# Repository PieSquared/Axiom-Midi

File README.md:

# Axiom-Midi
a Professional customizable MIDI Keyboard made by PieSquared. Has 1 octave worth of touch buttons (12 Key), 12 LEDs below them, 2 Push button rotary encoders, 6 Buttons, and a 0.96in LCD. Requires software to run and customize

## Why did I make this project

I mainly wanted to challenge myself and see what I could do without using a devkit, and what better way to do this by making something about what I love, Music!

Onshape Document: https://cad.onshape.com/documents/4fcb2e2092c7b8f6c2e7c126/w/a1f5aab5071a20b775f20b63/e/1a1cbc1f4bd564a001b92cae

## Features
- Customizable keys (Mainly used for soundboard)
- 12 touch keys
- 2 Pushbutton Rotary Encoders (Can be used for Octave changes, ect.)
- LCD
- Customizable LEDs
- Custom firmware
- Small formfactor

## Pictures

## BOM

| Part | Quantity |
|---|---:|
| 0.96 inch OLED IIC white 128x64 | 1 |
| EC11 rotary encoder right-angle with switch | 2 |
| Kailh Low Profile Choc switch 1350 clicky tactile | 6 |
| EC11 knob (half handle black) | 2 |
| CFX Low Profile Choc PBT keycaps | 6 |
|Case| 1 |
|PCB| 1 |

For purchase cost and purchase links refer to BOM.csv

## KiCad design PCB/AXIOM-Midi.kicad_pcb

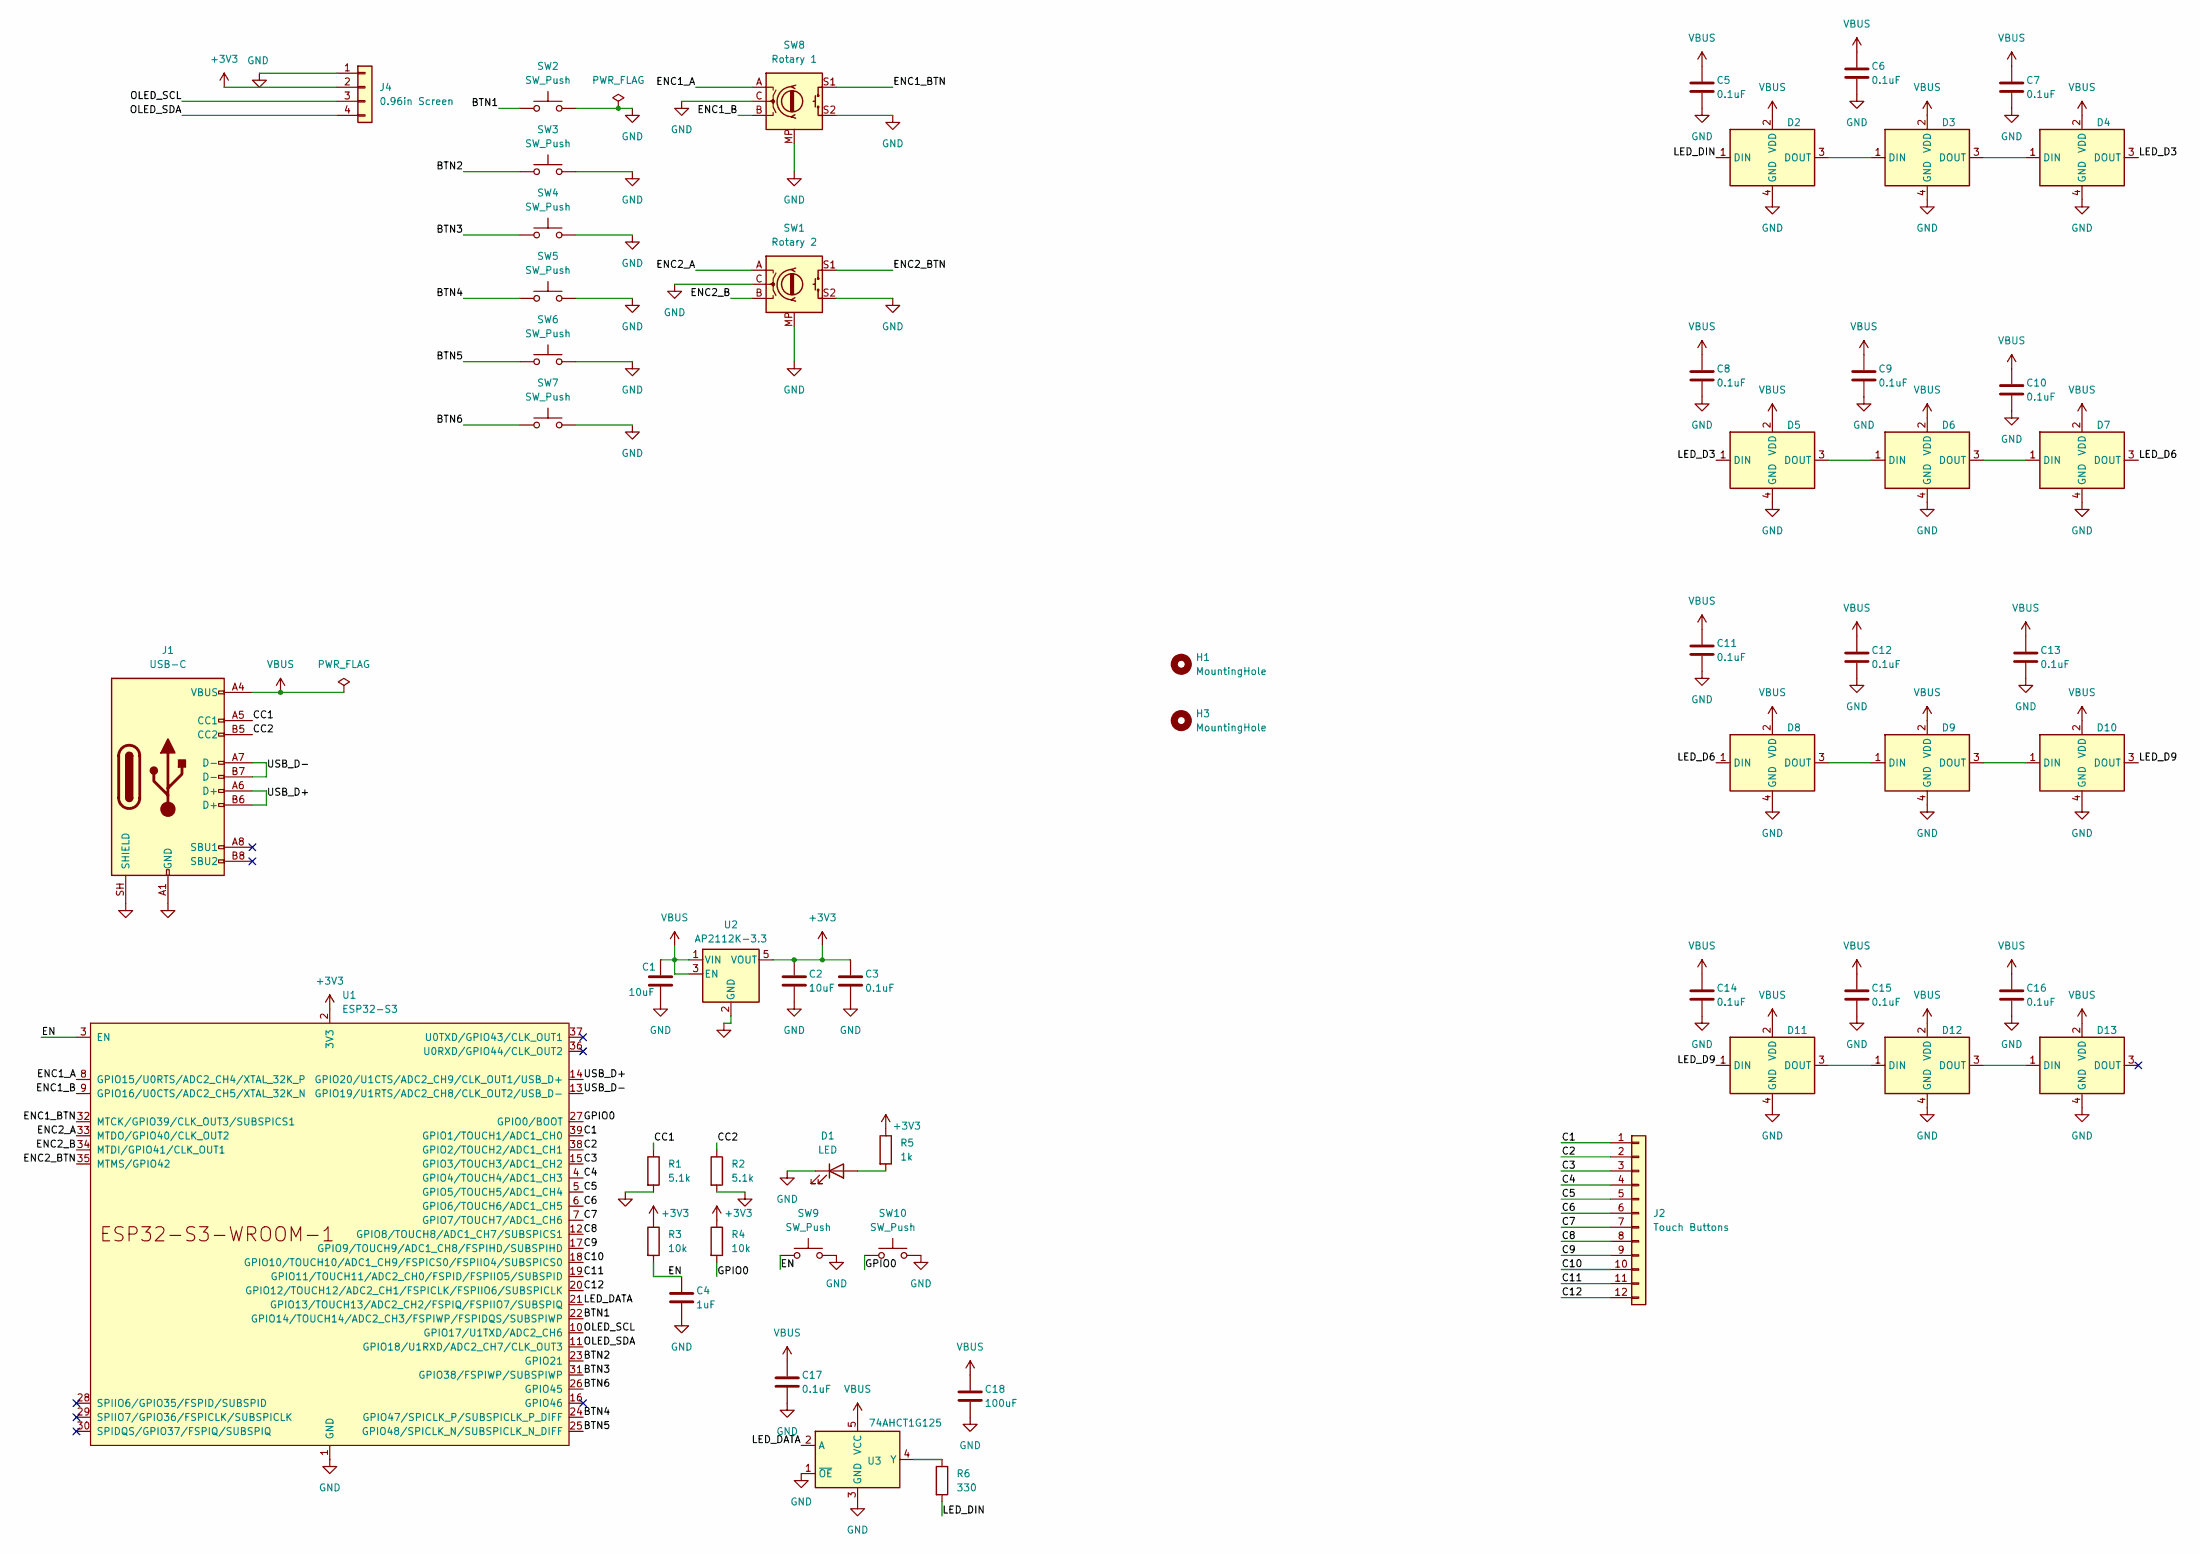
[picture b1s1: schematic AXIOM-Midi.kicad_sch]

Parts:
C1, C2: 10uF; C_0805_2012Metric
C3, C5, C6, C7, C8, C9, C10, C11, C12, C13, C14, C15, C16, C17: 0.1uF; C_0603_1608Metric
C4: 1uF; C_0603_1608Metric
C18: 100uF; CP_Elec_6.3x5.4
D1: LED; LED_0603_1608Metric
D2, D3, D4, D5, D6, D7, D8, D9, D10, D11, D12, D13: SK6812SIDE-A; LED-SMD_4P-L4.0-W1.6-L
H1, H3: MountingHole; MountingHole_3mm
J1: USB-C; USB_C_Receptacle_HRO_TYPE-C-31-M-12
J2: Touch Buttons; Piano_12Key
J4: 0.96in Screen; PinSocket_1x04_P2.54mm_Vertical
R1, R2: 5.1k; R_0603_1608Metric
R3, R4: 10k; R_0603_1608Metric
R5: 1k; R_0603_1608Metric
R6: 330; R_0603_1608Metric
SW1: Rotary 2; RotaryEncoder_Alps_EC11E-Switch_Vertical_H20mm
SW2, SW3, SW4, SW5, SW6, SW7: SW_Push; Kailh Choc Low-Profile Switches
SW8: Rotary 1; RotaryEncoder_Alps_EC11E-Switch_Vertical_H20mm
SW9, SW10: SW_Push; SW_SPST_TL3342
U1: ESP32-S3; ESP32-S3-WROOM-1
U2: AP2112K-3.3; SOT-23-5
U3: 74AHCT1G125; SOT-23-5

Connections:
+3V3: C2.1, C3.1, J4.2, R3.1, R4.1, R5.1, U1.2 (3V3), U2.5 (VOUT)
/BTN1: SW2.1, U1.22 (GPIO14/TOUCH14/ADC2_CH3/FSPIWP/FSPIDQS/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)
/BTN2: SW3.1, U1.23 (GPIO21)
/BTN3: SW4.1, U1.31 (GPIO38/FSPIWP/SUBSPIWP)
/BTN4: SW5.1, U1.24 (GPIO47/SPICLK_P/SUBSPICLK_P_DIFF)
/BTN5: SW6.1, U1.25 (GPIO48/SPICLK_N/SUBSPICLK_N_DIFF)
/BTN6: SW7.1, U1.26 (GPIO45)
/C1: J2.1, U1.39 (GPIO1/TOUCH1/ADC1_CH0)
/C2: J2.2, U1.38 (GPIO2/TOUCH2/ADC1_CH1)
/C3: J2.3, U1.15 (GPIO3/TOUCH3/ADC1_CH2)
/C4: J2.4, U1.4 (GPIO4/TOUCH4/ADC1_CH3)
/C5: J2.5, U1.5 (GPIO5/TOUCH5/ADC1_CH4)
/C6: J2.6, U1.6 (GPIO6/TOUCH6/ADC1_CH5)
/C7: J2.7, U1.7 (GPIO7/TOUCH7/ADC1_CH6)
/C8: J2.8, U1.12 (GPIO8/TOUCH8/ADC1_CH7/SUBSPICS1)
/C9: J2.9, U1.17 (GPIO9/TOUCH9/ADC1_CH8/FSPIHD/SUBSPIHD)
/C10: J2.10, U1.18 (GPIO10/TOUCH10/ADC1_CH9/FSPICS0/FSPIIO4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)
/C11: J2.11, U1.19 (GPIO11/TOUCH11/ADC2_CH0/FSPID/FSPIIO5/S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)
/C12: J2.12, U1.20 (GPIO12/TOUCH12/ADC2_CH1/FSPICLK/FSPIIO6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)
/CC1: J1.A5 (CC1), R1.1
/CC2: J1.B5 (CC2), R2.1
/EN: C4.1, R3.2, SW9.1, U1.3 (EN)
/ENC1_A: SW8.A, U1.8 (GPIO15/U0RTS/ADC2_CH4/XTAL_32K_P)
/ENC1_B: SW8.B, U1.9 (GPIO16/U0CTS/ADC2_CH5/XTAL_32K_N)
/ENC1_BTN: SW8.S1, U1.32 (MTCK/GPIO39/CLK_OUT3/SUBSPICS1)
/ENC2_A: SW1.A, U1.33 (MTDO/GPIO40/CLK_OUT2)
/ENC2_B: SW1.B, U1.34 (MTDI/GPIO41/CLK_OUT1)
/ENC2_BTN: SW1.S1, U1.35 (MTMS/GPIO42)
/GPIO0: R4.2, SW10.1, U1.27 (GPIO0/BOOT)
/LED_D3: D4.3 (DOUT), D5.1 (DIN)
/LED_D6: D7.3 (DOUT), D8.1 (DIN)
/LED_D9: D10.3 (DOUT), D11.1 (DIN)
/LED_DATA: U1.21 (GPIO13/TOUCH13/ADC2_CH2/FSPIQ/FSPIIO7/S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), U3.2 (A)
/LED_DIN: D2.1 (DIN), R6.2
/OLED_SCL: J4.3, U1.10 (GPIO17/U1TXD/ADC2_CH6)
/OLED_SDA: J4.4, U1.11 (GPIO18/U1RXD/ADC2_CH7/CLK_OUT3)
/USB_D+: J1.A6 (D+), J1.B6 (D+), U1.14 (GPIO20/U1CTS/ADC2_CH9/CLK_OUT1/USB_D+)
/USB_D-: J1.A7 (D-), J1.B7 (D-), U1.13 (GPIO19/U1RTS/ADC2_CH8/CLK_OUT2/USB_D-)
GND: C1.2, C2.2, C3.2, C4.2, C5.2, C6.2, C7.2, C8.2, C9.2, C10.2, C11.2, C12.2, C13.2, C14.2, C15.2, C16.2, C17.2, C18.2, D1.1 (K), D2.4 (GND), D3.4 (GND), D4.4 (GND), D5.4 (GND), D6.4 (GND), D7.4 (GND), D8.4 (GND), D9.4 (GND), D10.4 (GND), D11.4 (GND), D12.4 (GND), D13.4 (GND), J1.A1 (GND), J1.A12 (GND), J1.B1 (GND), J1.B12 (GND), J1.SH (SHIELD), J4.1, R1.2, R2.2, SW1.C, SW1.MP, SW1.S2, SW2.2, SW3.2, SW4.2, SW5.2, SW6.2, SW7.2, SW8.C, SW8.MP, SW8.S2, SW9.2, SW10.2, U1.1 (GND), U1.40 (GND), U1.41 (GND), U2.2 (GND), U3.1 (~OE), U3.3 (GND)
unnamed: D1.2 (A), R5.2
unnamed: D2.3 (DOUT), D3.1 (DIN)
unnamed: D3.3 (DOUT), D4.1 (DIN)
unnamed: D5.3 (DOUT), D6.1 (DIN)
unnamed: D6.3 (DOUT), D7.1 (DIN)
unnamed: D8.3 (DOUT), D9.1 (DIN)
unnamed: D9.3 (DOUT), D10.1 (DIN)
unnamed: D11.3 (DOUT), D12.1 (DIN)
unnamed: D12.3 (DOUT), D13.1 (DIN)
unnamed: R6.1, U3.4 (Y)
VBUS: C1.1, C5.1, C6.1, C7.1, C8.1, C9.1, C10.1, C11.1, C12.1, C13.1, C14.1, C15.1, C16.1, C17.1, C18.1, D2.2 (VDD), D3.2 (VDD), D4.2 (VDD), D5.2 (VDD), D6.2 (VDD), D7.2 (VDD), D8.2 (VDD), D9.2 (VDD), D10.2 (VDD), D11.2 (VDD), D12.2 (VDD), D13.2 (VDD), J1.A4 (VBUS), J1.A9 (VBUS), J1.B4 (VBUS), J1.B9 (VBUS), U2.1 (VIN), U2.3 (EN), U3.5 (VCC)

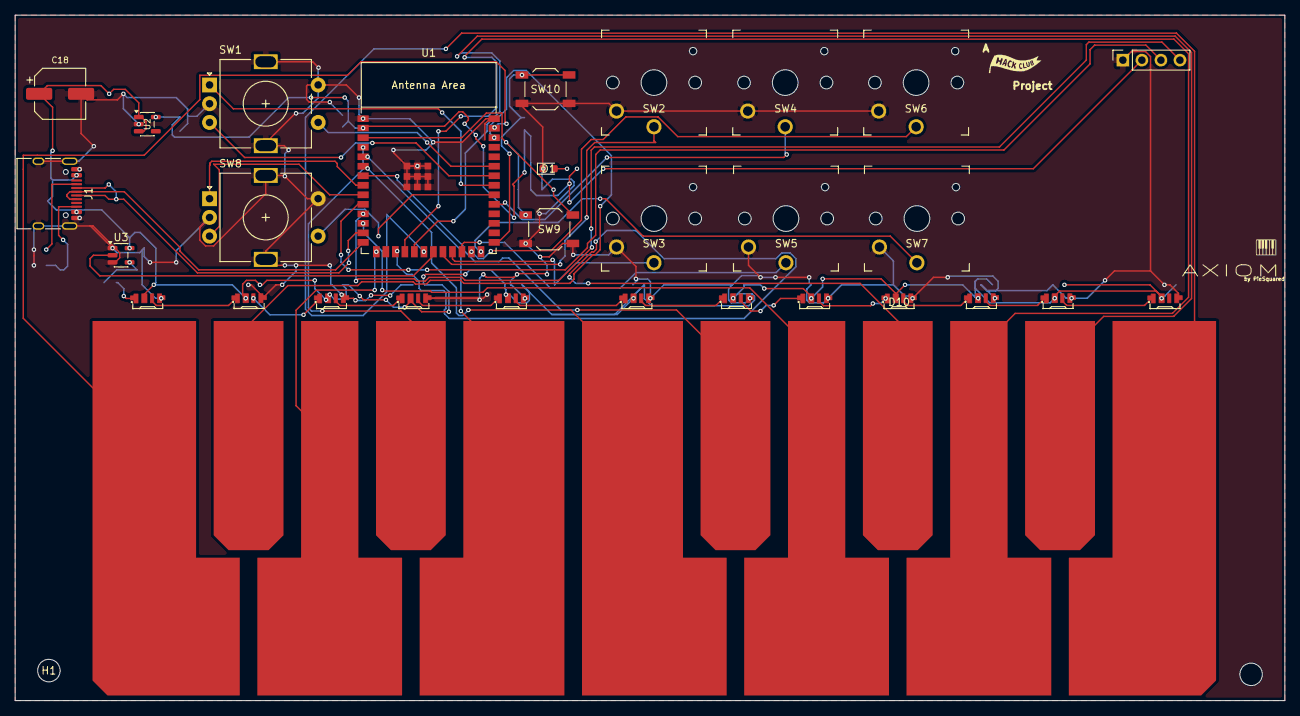
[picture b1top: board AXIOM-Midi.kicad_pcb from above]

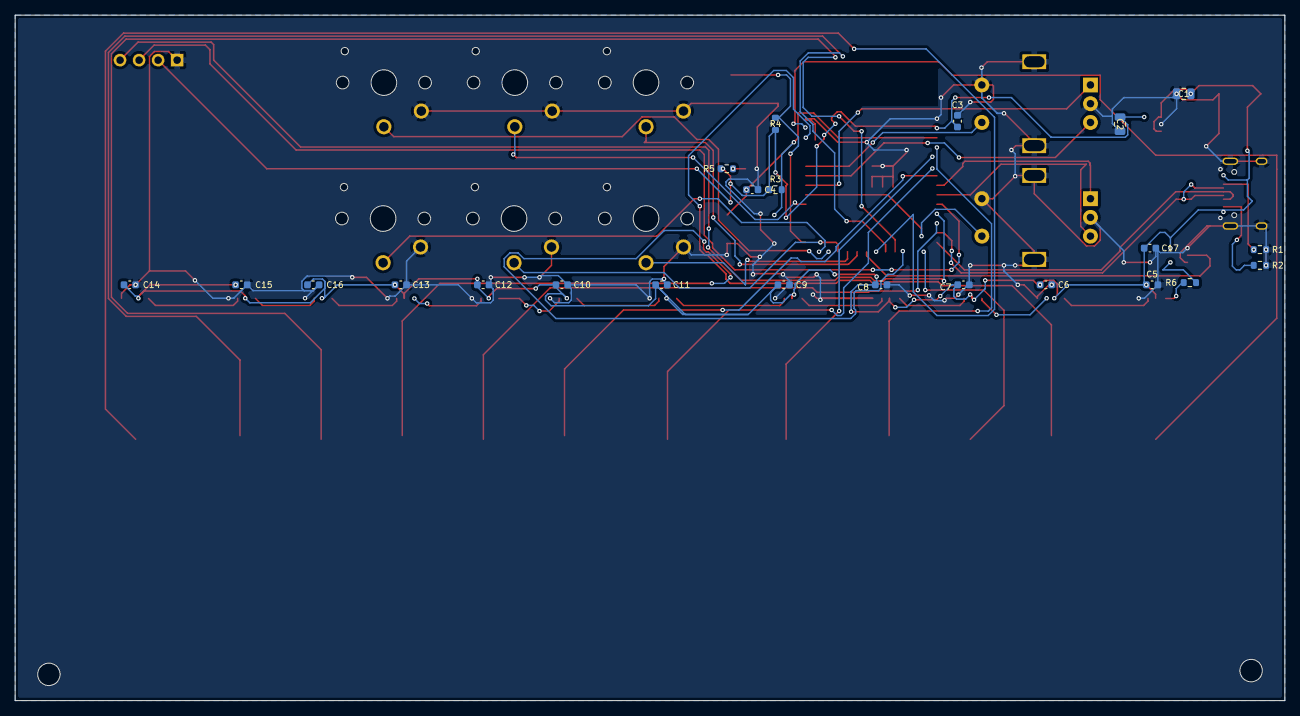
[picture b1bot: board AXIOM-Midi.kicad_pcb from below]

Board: 2 copper layers, 169.5 x 91.5 mm, 55 parts (23 on the bottom side), 50 nets.
